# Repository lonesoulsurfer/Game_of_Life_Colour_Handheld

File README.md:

Version 2 now includes the following tools:

	Sound: ON/OFF
	
	Volume: Low/Medium/High
	
	World: Toroid/Open
	
	Grid: ON/OFF
	
	Population: ON/OFF
	
	Trail Mode: ON/OFF

I have also included another alternative game called 'larger than life'.  This game uses larger neighbourhoods instead of just the immediate 8 neighbours.  You can check out the neighbour sizes by holding down button B!

Instructables - https://www.instructables.com/Conways-Game-of-Life-Handheld-COLOURED-Ve

Youtube - https://youtu.be/rWrENXPgask

Conway's Game of Life - Complete User Guide

Main Menu Navigation
    UP/DOWN: Navigate menu options
    
    B: Select menu item
    
    B: Go back to previous menu

Color Modes

	All game modes support color! Press UP + DOWN together to toggle.

Tools

Tools Menu Breakdown

	Sound: ON/OFF - Toggles all game sounds on or off

	Volume: Low/Medium/High

	World: Toroid/Open - Controls what happens at the edges of the game board
		
		Toroid = Wraparound edges (cells on the left edge are neighbors with cells on right edge, top wraps to bottom)
	
		Open = Hard edges (cells at the edge have fewer neighbors, no wraparound)
	
		Applies to ALL game modes (Conway's Life, Brian's Brain, Day & Night, Seeds, Cyclic CA)
	
		Default: Toroid (wraparound)

	Grid: ON/OFF - Shows/hides grid lines between cells
	
		Only visible when cell size is 3px or larger (not on Tiny 2px cells)
	
		Population: ON/OFF - Shows/hides the population counter overlay during gameplay

	Gen: Current generation number
	
		Pop: Current number of living cells

	Trail Mode: ON/OFF - Shows fading trails behind cells as they die
		
		In Mono mode = Gray fading trail (white → light gray → dark gray → black over 12 frames)
		
		In Color mode = Colored fading trail using age-based colors

During Gameplay

    UP: Increase speed (faster generations)
    
    DOWN: Decrease speed (slower generations)
    
    LEFT: Change cell size (Tiny → Small → Normal → Large)
    
    RIGHT: ReB/Regenerate current pattern
    
    UP + DOWN (together): Toggle COLOR/MONO mode
    
    B (short press): Return to menu
    
    B (2 second press): Show/hide game rules overlay

    RESET Button (hold 2 seconds): Enter bootloader mode for updates

Edit Mode (Custom games)

	D-Pad: Move cursor
	
	B (short press): Toggle cell on/off
	
	B (2 second press): Start game
	
	B: Return to menu

Main Menu Options
	PRESET - Classic Patterns
	
	Coe Ship - Spaceship that travels across the board
	
	Gosper Glider Gun - Continuously spawns gliders
	
	Diamond - 4-8-12 diamond pattern that evolves
	
	Pulsar - Achim's p144 oscillator (period-144 pattern)
	
	Glider - 56P6H1V0 spaceship pattern

RANDOM - Chaotic Evolution

	Unpredictable patterns emerge
	
	May stabilize into oscillators
	
	May die out completely
	
	Game shows statistics when it stabilizes or dies

SYMMETRIC -  Creates symmetric initial patterns with different sizes

	CUSTOM - Draw Your Own
	
	Step 1: Choose Cell Size
	
	Tiny (2px cells): 160x120 grid
	
	Small (3px cells): 106x80 grid
	
	Normal (4px cells): 80x60 grid
	
	Large (8px cells): 40x30 grid

Step 2: Edit Mode

	Red crosshair shows cursor position
	
	Cursor blinks at 4Hz for visibility
	
	White cells = alive, Black = dead
	
	Move with D-pad, toggle cells with B

Step 3: Run

	Hold B for 2 seconds to start
	
	While running, hold B for 800ms to return to edit mode
	
	Press B to return to menu

ALT GAMES - Alternative Cellular Automata

BRIAN'S BRAIN
	Small: Compact symmetric cluster
	
	Medium: Larger symmetric pattern (35% density)
	
	Large: Very large sparse pattern (18% density)
	
	Random: Scattered center-weighted distribution
	
	Custom: Draw your own pattern

DAY & NIGHT - Complementary rule B where birth/survival rules mirror each other.
	
	Very stable, creates intricate patterns
	
	Day/Night metaphor in color mode
	
	Often runs indefinitely

SEEDS - "Exploding" automaton where cells live for exactly 1 generation.
	
	Random: Auto-generated 4-way symmetric pattern
	
	Custom: Draw your own (choose cell size first)

CYCLIC CA - Multi-state cellular automaton where cells cycle through 6 states.

	VrtclSym: Vertical mirror symmetry
	
	4WayRot: 4-way rotational symmetry
	
	Random: Random pattern type and size

RULE EXPLORER - Create Custom Rules

	Choose from 9 famous rule variations:

	Conway (B3/S23) - Classic Game of Life

	HighLife (B36/S23) - Like Conway, with replicators

	Maze (B3/S12345) - Creates maze-like patterns

	Coral (B3/S45678) - Grows coral-like structures

	Seeds (B2/S) - Exploding patterns (same as Seeds mode)

	Replicator (B1357/S1357) - Self-replicating patterns

	2x2 (B36/S125) - Stable 2x2 blocks common

	NoDeath (B3/S012345678) - Cells never die once born

	Diamoeba (B35678/S5678) - Diamond-shaped amoebas

Custom Rules - Create your own rules:

	Navigation:
	
	UP/DOWN: Switch between Birth and Survival rows
	
	LEFT/RIGHT: Move cursor (0-8 neighbors)
	
	B (short): Toggle number on/off
	
	B (2 seconds): Start game with custom rules
	
	B: Back to preset menu

How It Works:

	Birth row: Select how many neighbors cause birth (0-8)
	
	Survival row: Select how many neighbors keep cell alive (0-8)
	
	Example: Conway's Life is B3 (birth on 3) / S23 (survive on 2 or 3)

Color Modes

	All game modes support color! Press UP + DOWN together to toggle.

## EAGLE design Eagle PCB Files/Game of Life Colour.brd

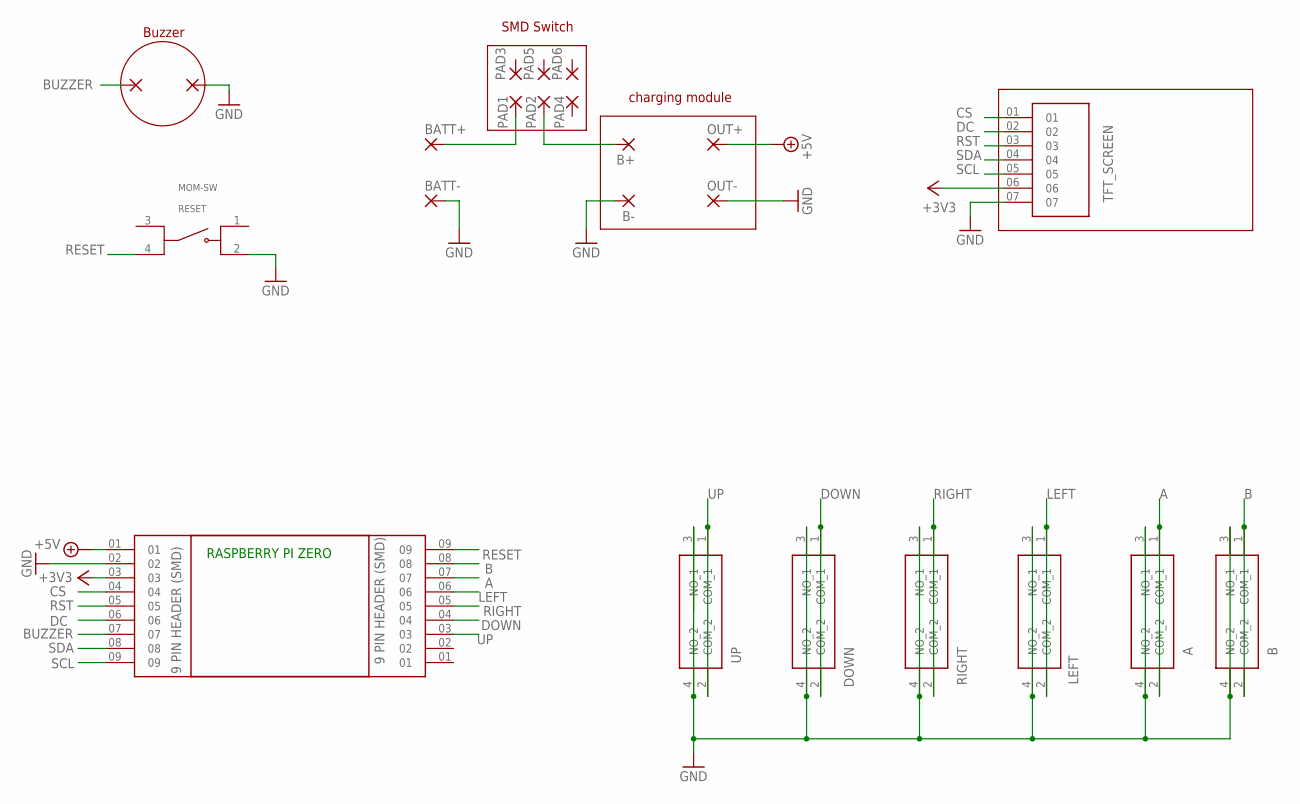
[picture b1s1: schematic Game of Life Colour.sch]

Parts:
A: 101-0364-EV; 1010364EV
B: 101-0364-EV; 1010364EV
B+: SMD5; SMD2,54-5,08
B-: SMD5; SMD2,54-5,08
BATT+: SMD5; SMD2,54-5,08
BATT-: SMD5; SMD2,54-5,08
DOWN: 101-0364-EV; 1010364EV
J2, J3: 9 PIN HEADER (SMD); SAMTEC_TMM-108-X-X-S-SM
LEFT: 101-0364-EV; 1010364EV
OUT+: SMD5; SMD2,54-5,08
OUT-: SMD5; SMD2,54-5,08
PAD1, PAD2, PAD3, PAD4, PAD5, PAD6, PAD7, PAD8: SMD2; SMD1,27-2,54
RESET: MOM-SW; SW_TS18-5-25-SL-260-SMT-TR
RIGHT: 101-0364-EV; 1010364EV
TFT_SCREEN: TMM-108-X-X-S-SM; SAMTEC_TMM-108-X-X-S-SM
UP: 101-0364-EV; 1010364EV

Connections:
+3V3: J3.03, TFT_SCREEN.06
+5V: J3.01, OUT+.1
A: A.1 (COM_1), A.2 (COM_2), J2.07
B: B.1 (COM_1), B.2 (COM_2), J2.08
BUZZER: J3.07, PAD7.1
CS: J3.04, TFT_SCREEN.01
DC: J3.06, TFT_SCREEN.02
DOWN: DOWN.1 (COM_1), DOWN.2 (COM_2), J2.04
GND: A.3 (NO_1), A.4 (NO_2), B.3 (NO_1), B.4 (NO_2), B-.1, BATT-.1, DOWN.3 (NO_1), DOWN.4 (NO_2), J3.02, LEFT.3 (NO_1), LEFT.4 (NO_2), OUT-.1, PAD8.1, RESET.2, RIGHT.3 (NO_1), RIGHT.4 (NO_2), TFT_SCREEN.07, UP.3 (NO_1), UP.4 (NO_2)
LEFT: J2.06, LEFT.1 (COM_1), LEFT.2 (COM_2)
unnamed: BATT+.1, PAD1.1
unnamed: B+.1, PAD2.1
RESET: J2.09, RESET.4
RIGHT: J2.05, RIGHT.1 (COM_1), RIGHT.2 (COM_2)
RST: J3.05, TFT_SCREEN.03
SCL: J3.09, TFT_SCREEN.05
SDA: J3.08, TFT_SCREEN.04
UP: J2.03, UP.1 (COM_1), UP.2 (COM_2)

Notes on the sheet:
charging module
SMD Switch
Buzzer
RASPBERRY PI ZERO

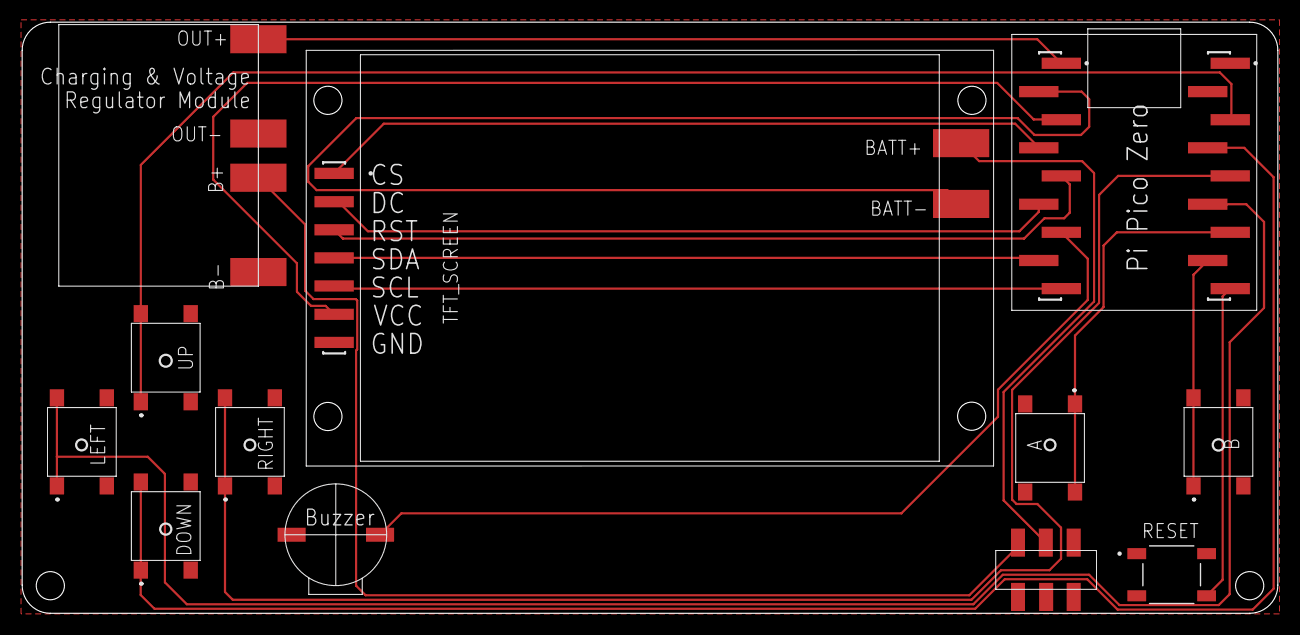
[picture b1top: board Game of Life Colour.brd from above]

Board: 2 copper layers, 113.3 x 53.3 mm, 24 parts (0 on the bottom side), 18 nets.

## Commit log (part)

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2026-01-03 Format README for better readability
2026-01-03 Add descriptions for Brian's Brain patterns
2026-01-03 Add color mode instructions to README
    Added instructions for toggling color modes in the game.
2026-01-03 Update README with additional resource links
    Added links to Instructables and YouTube for Conway's Game of Life.
2026-01-05 Enhance README with tools and gameplay information
    Added tools menu breakdown and gameplay controls to README.
2026-01-05 Add volume control option to README
2026-01-05 Revise gameplay and edit mode instructions
    Updated gameplay instructions and options in README.
